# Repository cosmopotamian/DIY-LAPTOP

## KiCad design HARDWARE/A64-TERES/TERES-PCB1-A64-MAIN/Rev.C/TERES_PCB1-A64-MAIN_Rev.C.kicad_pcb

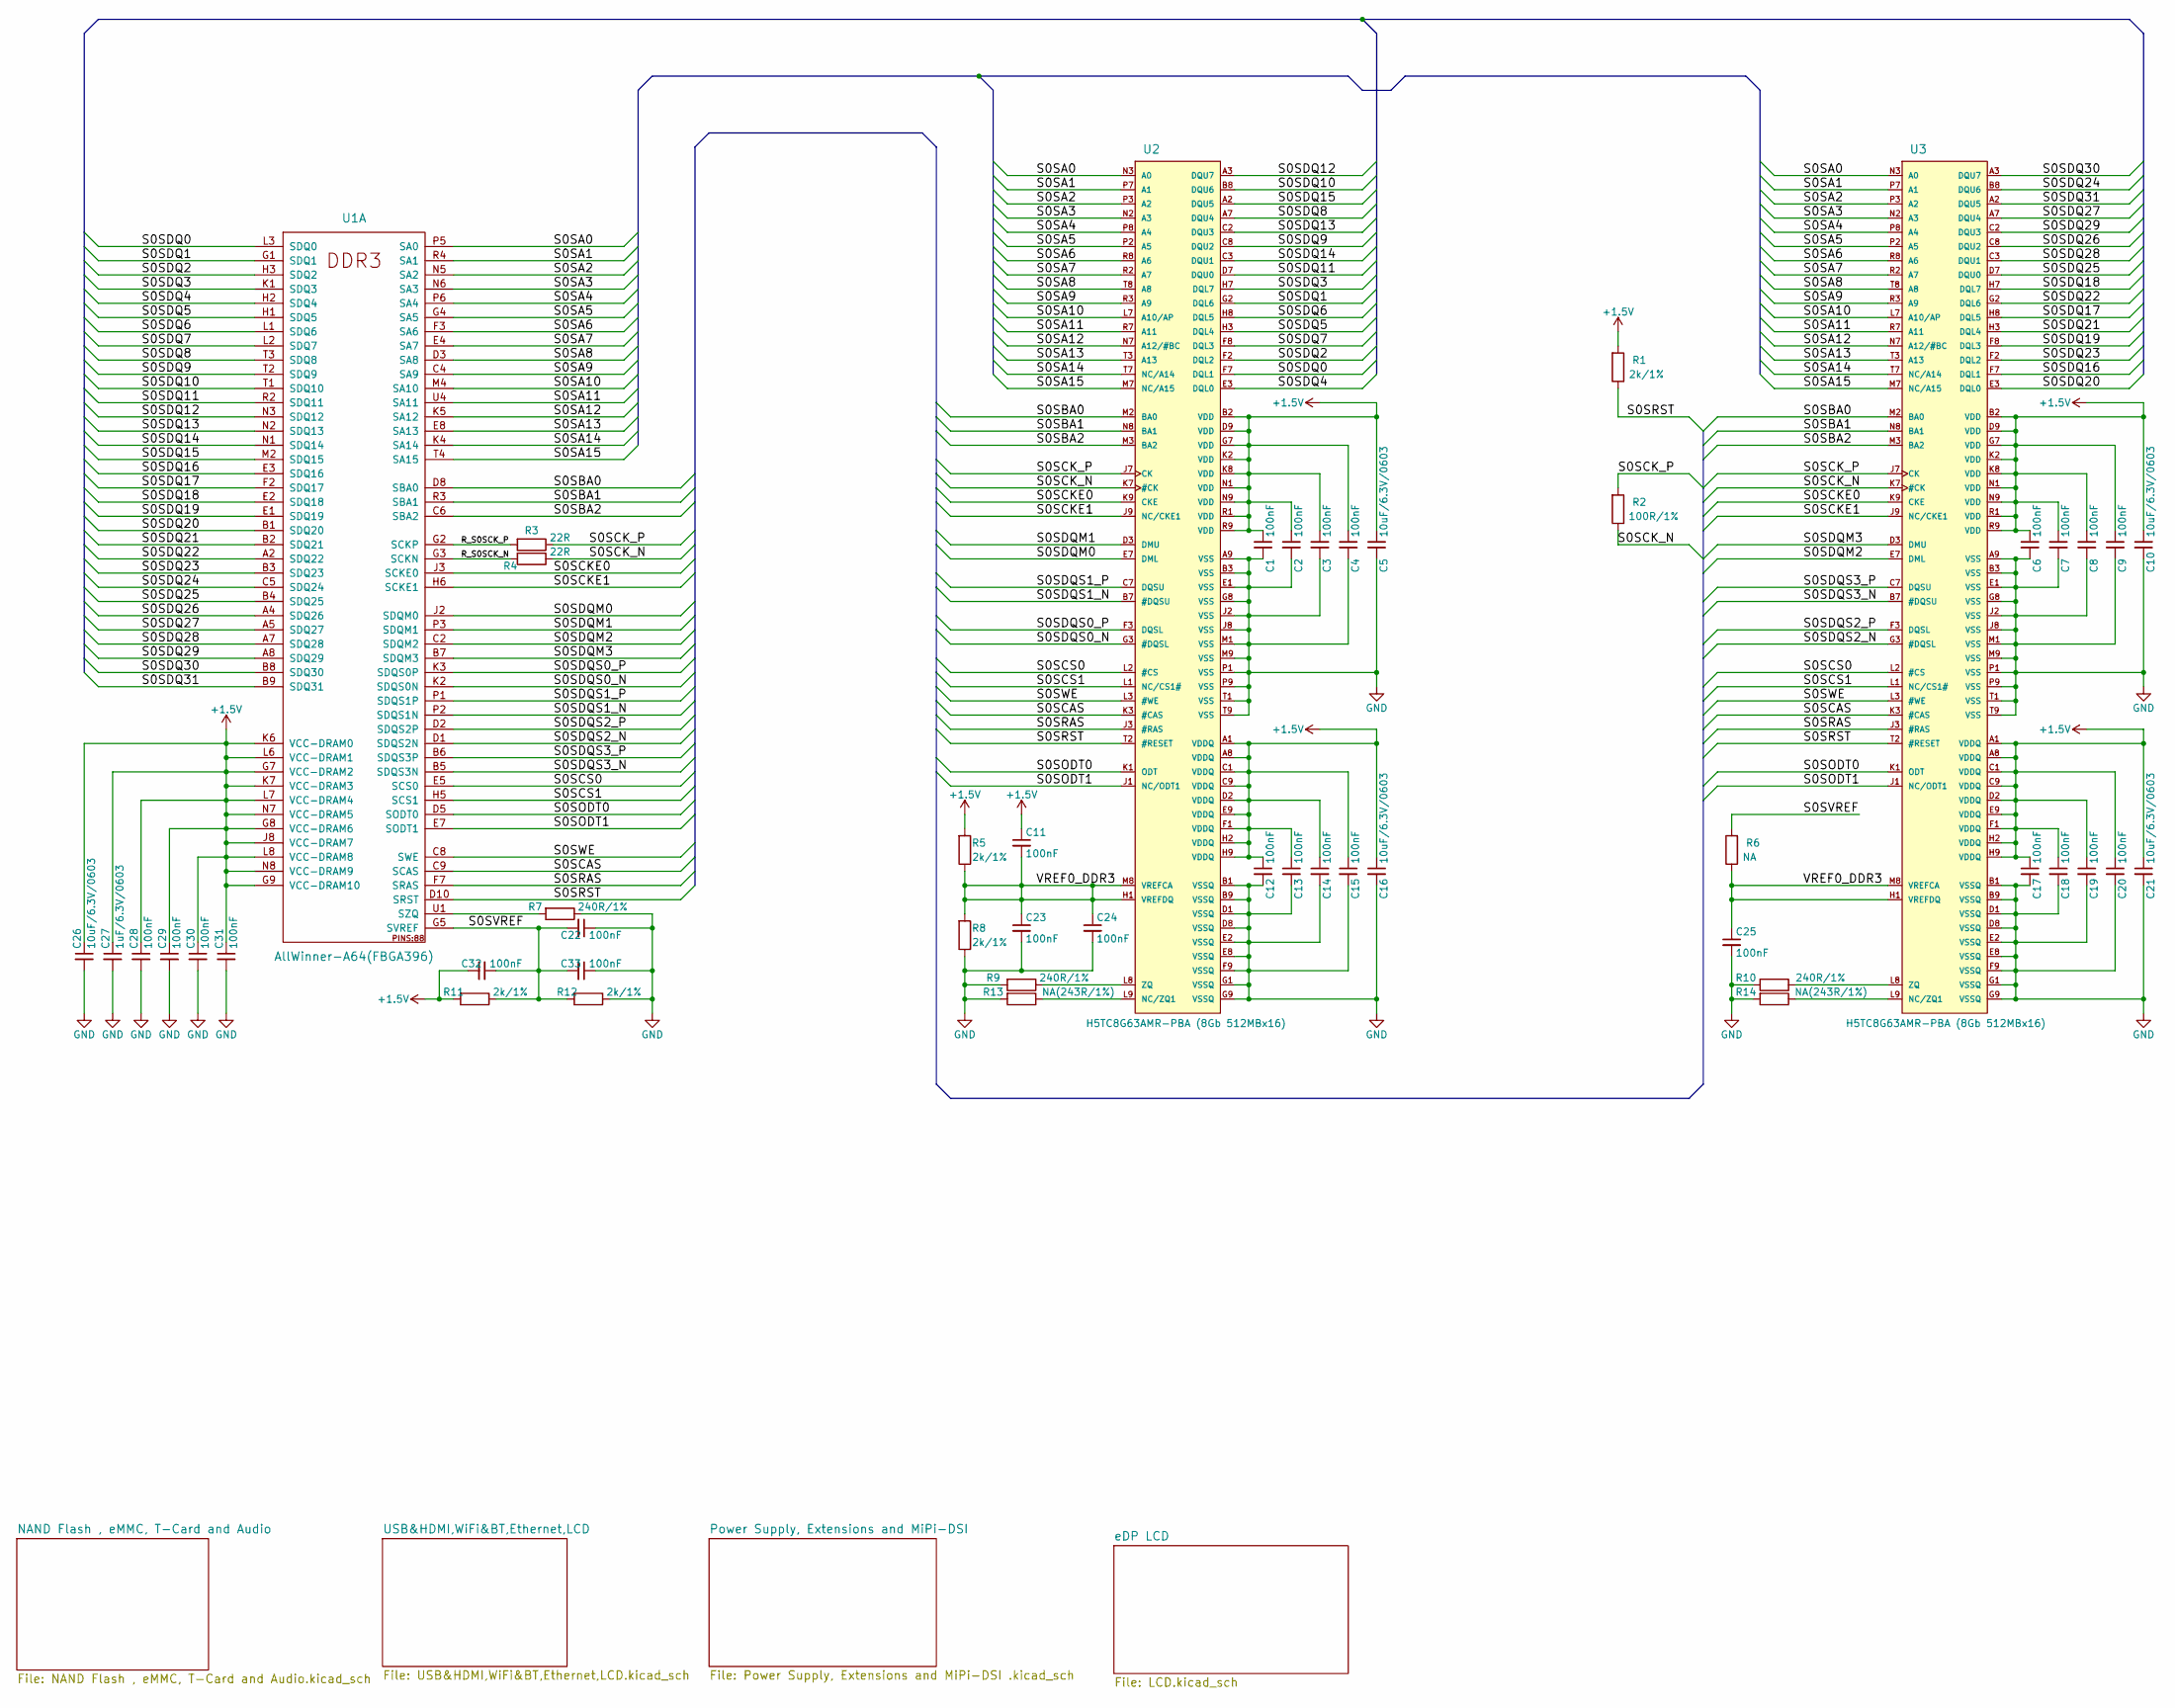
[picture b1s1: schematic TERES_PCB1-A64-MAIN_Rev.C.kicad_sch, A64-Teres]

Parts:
C1, C2, C3, C4, C6, C7, C8, C9, C11, C12, C13, C14, C15, C17, C18, C19, C20, C22, C23, C24, C25, C28, C29, C30, C31, C32, C33: 100nF; C_0402_5MIL_DWS
C5, C10, C16, C21, C26: 10uF/6.3V/0603; C_0603_5MIL_DWS
C27: 1uF/6.3V/0603; C_0603_5MIL_DWS
R1, R5, R8, R11, R12: 2k/1%; R_0402_5MIL_DWS
R2: 100R/1%; R_0402_5MIL_DWS
R3, R4: 22R; R_0402_5MIL_DWS
R6: NA; R_0402_5MIL_DWS
R7, R9, R10: 240R/1%; R_0402_5MIL_DWS
R13, R14: NA(243R/1%); R_0402_5MIL_DWS
U1: AllWinner-A64(FBGA396); FBGA396
U2, U3: H5TC8G63AMR-PBA (8Gb 512MBx16); FBGA96(HYNIX_SAMSUNG_512MX16_DDR3)

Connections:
+1.5V: C1.1, C2.1, C3.1, C4.1, C5.1, C6.1, C7.1, C8.1, C9.1, C10.1, C11.1, C12.1, C13.1, C14.1, C15.1, C16.1, C17.1, C18.1, C19.1, C20.1, C21.1, C26.1, C27.1, C28.1, C29.1, C30.1, C31.1, C32.2, R1.2, R5.2, R11.2, U1.G7 (VCC-DRAM2), U1.G8 (VCC-DRAM6), U1.G9 (VCC-DRAM10), U1.J8 (VCC-DRAM7), U1.K6 (VCC-DRAM0), U1.K7 (VCC-DRAM3), U1.L6 (VCC-DRAM1), U1.L7 (VCC-DRAM4), U1.L8 (VCC-DRAM8), U1.N7 (VCC-DRAM5), U1.N8 (VCC-DRAM9), U2.A1 (VDDQ), U2.A8 (VDDQ), U2.B2 (VDD), U2.C1 (VDDQ), U2.C9 (VDDQ), U2.D2 (VDDQ), U2.D9 (VDD), U2.E9 (VDDQ), U2.F1 (VDDQ), U2.G7 (VDD), U2.H2 (VDDQ), U2.H9 (VDDQ), U2.K2 (VDD), U2.K8 (VDD), U2.N1 (VDD), U2.N9 (VDD), U2.R1 (VDD), U2.R9 (VDD), U3.A1 (VDDQ), U3.A8 (VDDQ), U3.B2 (VDD), U3.C1 (VDDQ), U3.C9 (VDDQ), U3.D2 (VDDQ), U3.D9 (VDD), U3.E9 (VDDQ), U3.F1 (VDDQ), U3.G7 (VDD), U3.H2 (VDDQ), U3.H9 (VDDQ), U3.K2 (VDD), U3.K8 (VDD), U3.N1 (VDD), U3.N9 (VDD), U3.R1 (VDD), U3.R9 (VDD); also elsewhere on the board
/R_S0SCK_N: R4.2, U1.G3 (SCKN)
/R_S0SCK_P: R3.2, U1.G2 (SCKP)
/S0SA0: U1.P5 (SA0), U2.N3 (A0), U3.N3 (A0)
/S0SA1: U1.R4 (SA1), U2.P7 (A1), U3.P7 (A1)
/S0SA2: U1.N5 (SA2), U2.P3 (A2), U3.P3 (A2)
/S0SA3: U1.N6 (SA3), U2.N2 (A3), U3.N2 (A3)
/S0SA4: U1.P6 (SA4), U2.P8 (A4), U3.P8 (A4)
/S0SA5: U1.G4 (SA5), U2.P2 (A5), U3.P2 (A5)
/S0SA6: U1.F3 (SA6), U2.R8 (A6), U3.R8 (A6)
/S0SA7: U1.E4 (SA7), U2.R2 (A7), U3.R2 (A7)
/S0SA8: U1.D3 (SA8), U2.T8 (A8), U3.T8 (A8)
/S0SA9: U1.C4 (SA9), U2.R3 (A9), U3.R3 (A9)
/S0SA10: U1.M4 (SA10), U2.L7 (A10/AP), U3.L7 (A10/AP)
/S0SA11: U1.U4 (SA11), U2.R7 (A11), U3.R7 (A11)
/S0SA12: U1.K5 (SA12), U2.N7 (A12/#BC), U3.N7 (A12/#BC)
/S0SA13: U1.E8 (SA13), U2.T3 (A13), U3.T3 (A13)
/S0SA14: U1.K4 (SA14), U2.T7 (NC/A14), U3.T7 (NC/A14)
/S0SA15: U1.T4 (SA15), U2.M7 (NC/A15), U3.M7 (NC/A15)
/S0SBA0: U1.D8 (SBA0), U2.M2 (BA0), U3.M2 (BA0)
/S0SBA1: U1.R3 (SBA1), U2.N8 (BA1), U3.N8 (BA1)
/S0SBA2: U1.C6 (SBA2), U2.M3 (BA2), U3.M3 (BA2)
/S0SCAS: U1.C9 (SCAS), U2.K3 (#CAS), U3.K3 (#CAS)
/S0SCKE0: U1.J3 (SCKE0), U2.K9 (CKE), U3.K9 (CKE)
/S0SCKE1: U1.H6 (SCKE1), U2.J9 (NC/CKE1), U3.J9 (NC/CKE1)
/S0SCK_N: R2.1, R4.1, U2.K7 (#CK), U3.K7 (#CK)
/S0SCK_P: R2.2, R3.1, U2.J7 (CK), U3.J7 (CK)
/S0SCS0: U1.E5 (SCS0), U2.L2 (#CS), U3.L2 (#CS)
/S0SCS1: U1.H5 (SCS1), U2.L1 (NC/CS1#), U3.L1 (NC/CS1#)
/S0SDQ0: U1.L3 (SDQ0), U2.F7 (DQL1)
/S0SDQ1: U1.G1 (SDQ1), U2.G2 (DQL6)
/S0SDQ2: U1.H3 (SDQ2), U2.F2 (DQL2)
/S0SDQ3: U1.K1 (SDQ3), U2.H7 (DQL7)
/S0SDQ4: U1.H2 (SDQ4), U2.E3 (DQL0)
/S0SDQ5: U1.H1 (SDQ5), U2.H3 (DQL4)
/S0SDQ6: U1.L1 (SDQ6), U2.H8 (DQL5)
/S0SDQ7: U1.L2 (SDQ7), U2.F8 (DQL3)
/S0SDQ8: U1.T3 (SDQ8), U2.A7 (DQU4)
/S0SDQ9: U1.T2 (SDQ9), U2.C8 (DQU2)
/S0SDQ10: U1.T1 (SDQ10), U2.B8 (DQU6)
/S0SDQ11: U1.R2 (SDQ11), U2.D7 (DQU0)
/S0SDQ12: U1.N3 (SDQ12), U2.A3 (DQU7)
/S0SDQ13: U1.N2 (SDQ13), U2.C2 (DQU3)
/S0SDQ14: U1.N1 (SDQ14), U2.C3 (DQU1)
/S0SDQ15: U1.M2 (SDQ15), U2.A2 (DQU5)
/S0SDQ16: U1.E3 (SDQ16), U3.F7 (DQL1)
/S0SDQ17: U1.F2 (SDQ17), U3.H8 (DQL5)
/S0SDQ18: U1.E2 (SDQ18), U3.H7 (DQL7)
/S0SDQ19: U1.E1 (SDQ19), U3.F8 (DQL3)
/S0SDQ20: U1.B1 (SDQ20), U3.E3 (DQL0)
/S0SDQ21: U1.B2 (SDQ21), U3.H3 (DQL4)
/S0SDQ22: U1.A2 (SDQ22), U3.G2 (DQL6)
/S0SDQ23: U1.B3 (SDQ23), U3.F2 (DQL2)
/S0SDQ24: U1.C5 (SDQ24), U3.B8 (DQU6)
/S0SDQ25: U1.B4 (SDQ25), U3.D7 (DQU0)
/S0SDQ26: U1.A4 (SDQ26), U3.C8 (DQU2)
/S0SDQ27: U1.A5 (SDQ27), U3.A7 (DQU4)
/S0SDQ28: U1.A7 (SDQ28), U3.C3 (DQU1)
/S0SDQ29: U1.A8 (SDQ29), U3.C2 (DQU3)
/S0SDQ30: U1.B8 (SDQ30), U3.A3 (DQU7)
/S0SDQ31: U1.B9 (SDQ31), U3.A2 (DQU5)
/S0SDQM0: U1.J2 (SDQM0), U2.E7 (DML)
/S0SDQM1: U1.P3 (SDQM1), U2.D3 (DMU)
/S0SDQM2: U1.C2 (SDQM2), U3.E7 (DML)
/S0SDQM3: U1.B7 (SDQM3), U3.D3 (DMU)
/S0SDQS0_N: U1.K2 (SDQS0N), U2.G3 (#DQSL)
/S0SDQS0_P: U1.K3 (SDQS0P), U2.F3 (DQSL)
/S0SDQS1_N: U1.P2 (SDQS1N), U2.B7 (#DQSU)
/S0SDQS1_P: U1.P1 (SDQS1P), U2.C7 (DQSU)
/S0SDQS2_N: U1.D1 (SDQS2N), U3.G3 (#DQSL)
/S0SDQS2_P: U1.D2 (SDQS2P), U3.F3 (DQSL)
/S0SDQS3_N: U1.B5 (SDQS3N), U3.B7 (#DQSU)
/S0SDQS3_P: U1.B6 (SDQS3P), U3.C7 (DQSU)
/S0SODT0: U1.D5 (SODT0), U2.K1 (ODT), U3.K1 (ODT)
/S0SODT1: U1.E7 (SODT1), U2.J1 (NC/ODT1), U3.J1 (NC/ODT1)
/S0SRAS: U1.F7 (SRAS), U2.J3 (#RAS), U3.J3 (#RAS)
/S0SRST: R1.1, U1.D10 (SRST), U2.T2 (#RESET), U3.T2 (#RESET)
/S0SVREF: C22.2, C32.1, C33.2, R6.2, R11.1, R12.2, U1.G5 (SVREF)
/S0SWE: U1.C8 (SWE), U2.L3 (#WE), U3.L3 (#WE)
/VREF0_DDR3: C11.2, C23.1, C24.1, C25.1, R5.1, R6.1, R8.2, U2.H1 (VREFDQ), U2.M8 (VREFCA), U3.H1 (VREFDQ), U3.M8 (VREFCA)
GND: C1.2, C2.2, C3.2, C4.2, C5.2, C6.2, C7.2, C8.2, C9.2, C10.2, C12.2, C13.2, C14.2, C15.2, C16.2, C17.2, C18.2, C19.2, C20.2, C21.2, C22.1, C23.2, C24.2, C25.2, C26.2, C27.2, C28.2, C29.2, C30.2, C31.2, C33.1, R7.1, R8.1, R9.2, R10.2, R12.1, R13.2, R14.2, U2.A9 (VSS), U2.B1 (VSSQ), U2.B3 (VSS), U2.B9 (VSSQ), U2.D1 (VSSQ), U2.D8 (VSSQ), U2.E1 (VSS), U2.E2 (VSSQ), U2.E8 (VSSQ), U2.F9 (VSSQ), U2.G1 (VSSQ), U2.G8 (VSS), U2.G9 (VSSQ), U2.J2 (VSS), U2.J8 (VSS), U2.M1 (VSS), U2.M9 (VSS), U2.P1 (VSS), U2.P9 (VSS), U2.T1 (VSS), U2.T9 (VSS), U3.A9 (VSS), U3.B1 (VSSQ), U3.B3 (VSS), U3.B9 (VSSQ), U3.D1 (VSSQ), U3.D8 (VSSQ), U3.E1 (VSS), U3.E2 (VSSQ), U3.E8 (VSSQ), U3.F9 (VSSQ), U3.G1 (VSSQ), U3.G8 (VSS), U3.G9 (VSSQ), U3.J2 (VSS), U3.J8 (VSS), U3.M1 (VSS), U3.M9 (VSS), U3.P1 (VSS), U3.P9 (VSS), U3.T1 (VSS), U3.T9 (VSS); also elsewhere on the board
unnamed: R7.2, U1.U1 (SZQ)
unnamed: R9.1, U2.L8 (ZQ)
unnamed: R10.1, U3.L8 (ZQ)
unnamed: R13.1, U2.L9 (NC/ZQ1)
unnamed: R14.1, U3.L9 (NC/ZQ1)

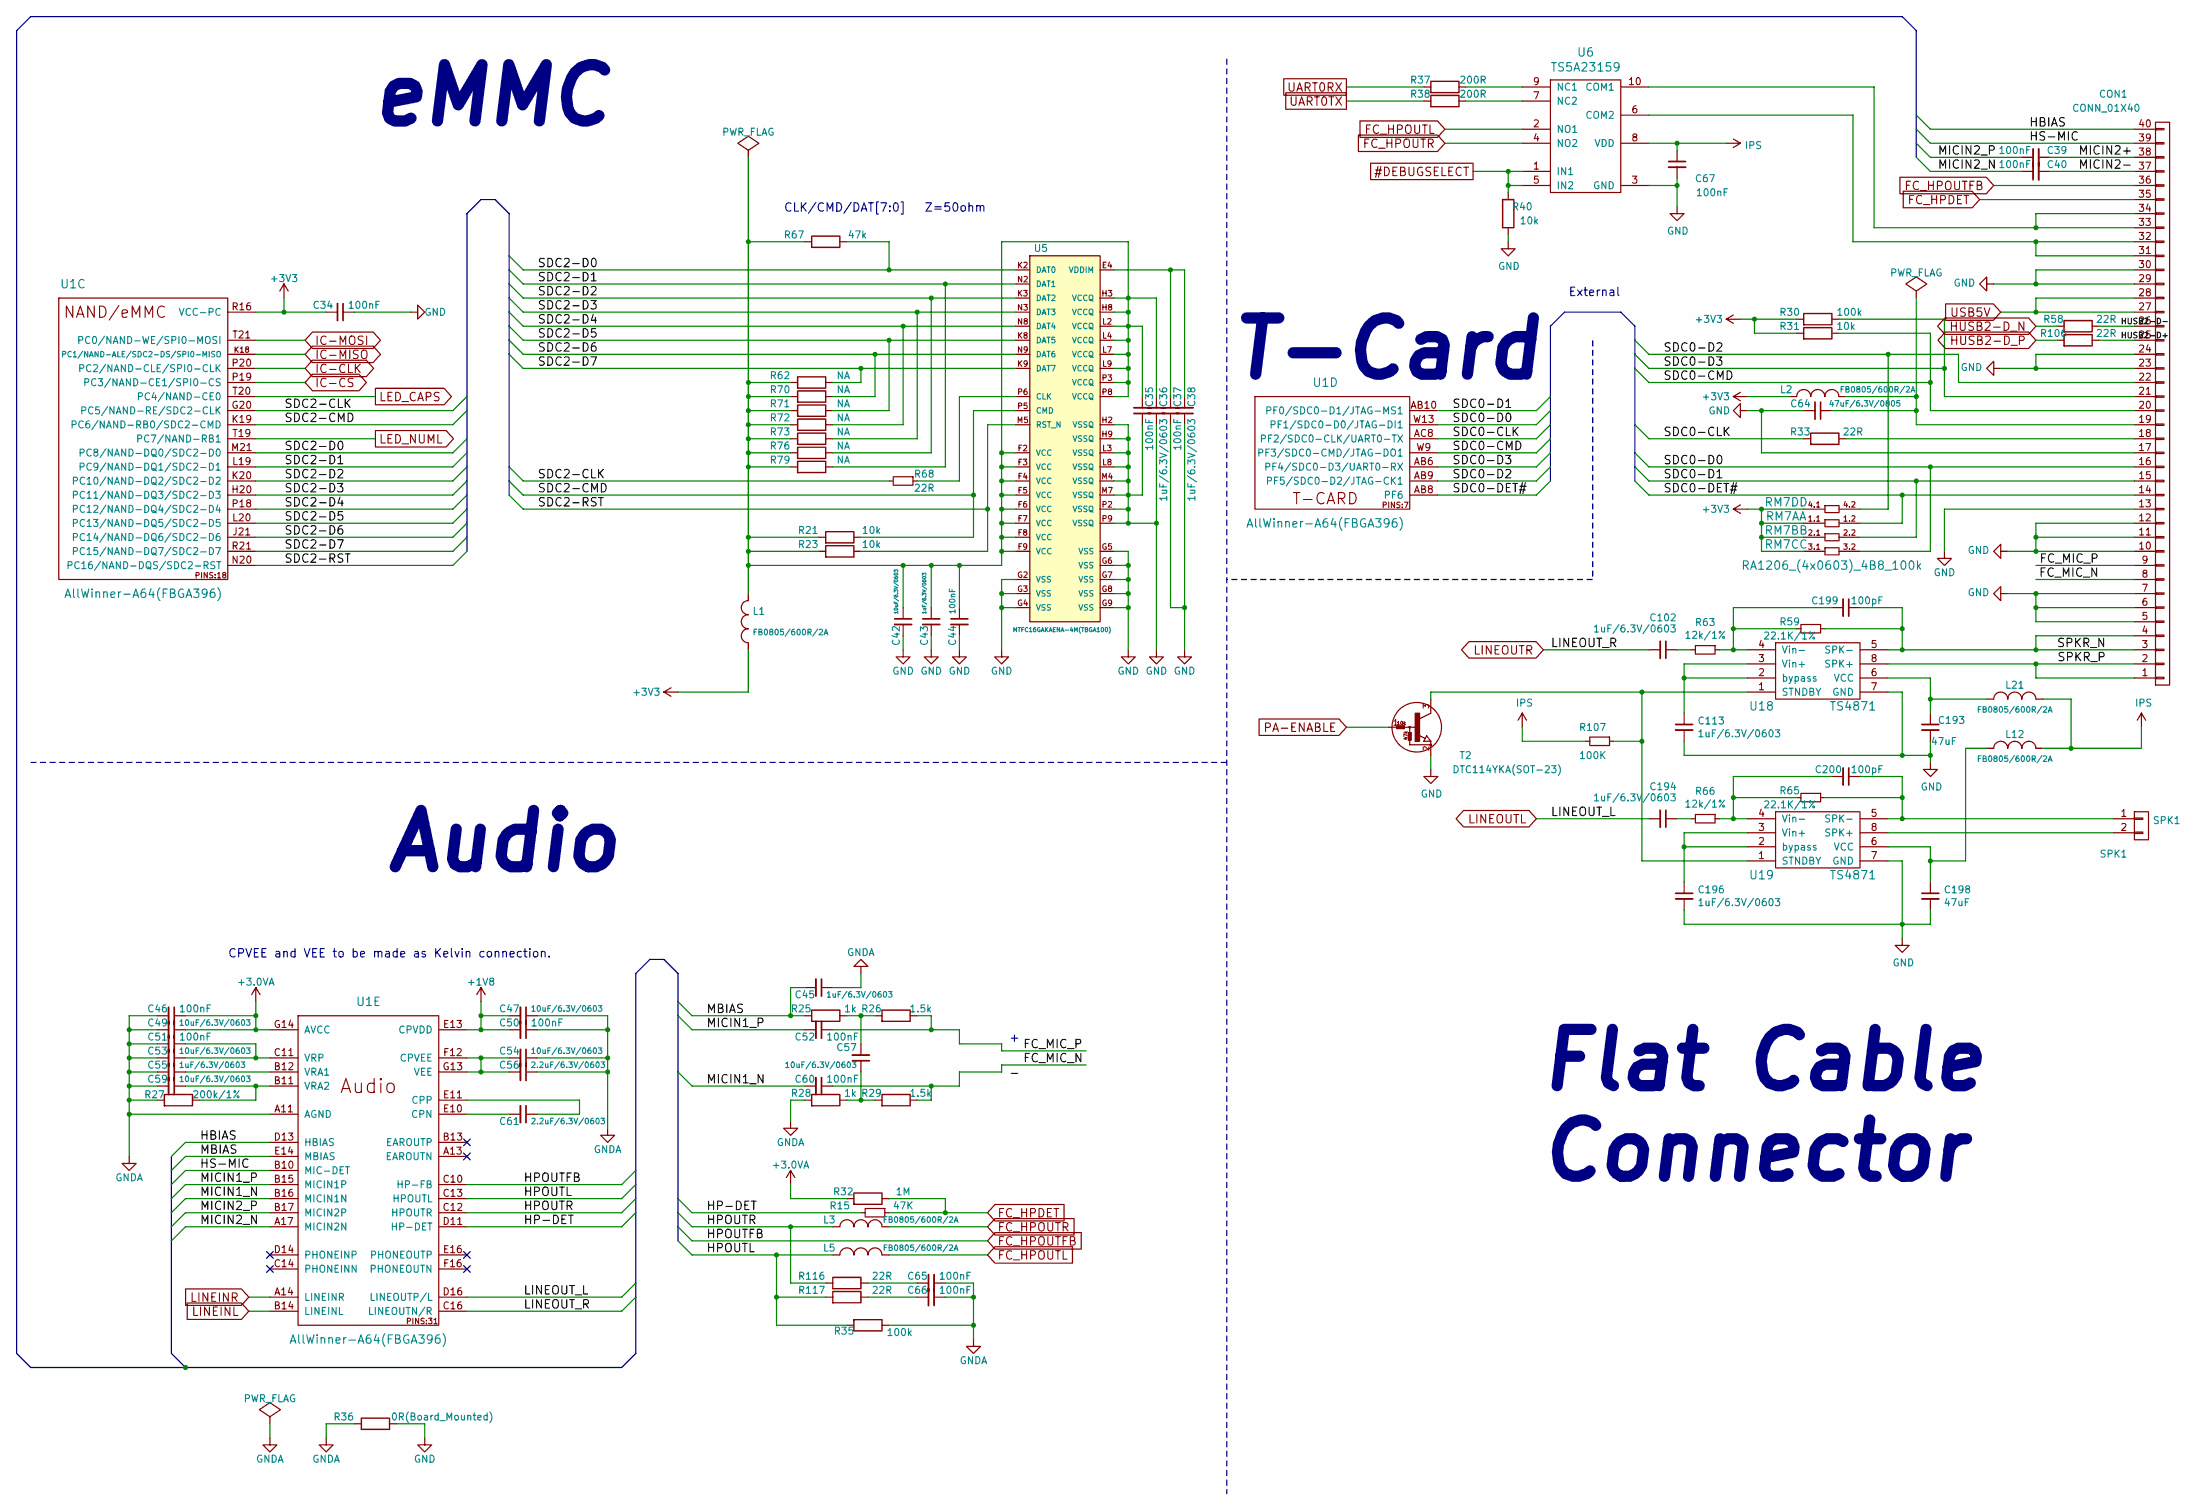
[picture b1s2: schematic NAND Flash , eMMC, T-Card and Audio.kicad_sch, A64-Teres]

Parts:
C34, C35, C37, C39, C40, C44, C46, C50, C51, C52, C60, C65, C66, C67: 100nF; C_0402_5MIL_DWS
C36, C38, C43, C45, C55, C102, C113, C194, C196: 1uF/6.3V/0603; C_0603_5MIL_DWS
C42, C47, C49, C53, C54, C57, C59: 10uF/6.3V/0603; C_0603_5MIL_DWS
C56, C61: 2.2uF/6.3V/0603; C_0603_5MIL_DWS
C64: 47uF/6.3V/0805; C_0805_5MIL_DWS
C193, C198: 47uF; C_0805_5MIL_DWS
C199, C200: 100pF; C_0402_5MIL_DWS
CON1: CONN_01X40; FPV-WZA21-40-LF
L1, L2, L3, L5, L12, L21: FB0805/600R/2A; L_0805_5MIL_DWS
R15: 47K; R_0402_5MIL_DWS
R21, R23, R31, R40: 10k; R_0402_5MIL_DWS
R25, R28: 1k; R_0402_5MIL_DWS
R26, R29: 1.5k; R_0402_5MIL_DWS
R27: 200k/1%; R_0402_5MIL_DWS
R30, R35: 100k; R_0402_5MIL_DWS
R32: 1M; R_0402_5MIL_DWS
R33, R58, R68, R106, R116, R117: 22R; R_0402_5MIL_DWS
R36: 0R(Board_Mounted); 0R_0603
R37, R38: 200R; R_0402_5MIL_DWS
R59, R65: 22.1K/1%; R_0402_5MIL_DWS
R62, R70, R71, R72, R73, R76, R79: NA; R_0402_5MIL_DWS
R63, R66: 12k/1%; R_0402_5MIL_DWS
R67: 47k; R_0402_5MIL_DWS
R107: 100K; R_0402_5MIL_DWS
RM7A, RM7B: RA1206_(4x0603)_4B8_100k; R_MATRIX_4
RM7C, RM7D: RA1206_(4x0603)_4B8_100k; RA1206_(4X0603)_4B8_xx
SPK1: SPK1; CON-SPK-TERES
T2: DTC114YKA(SOT-23); SOT23
U1: AllWinner-A64(FBGA396); FBGA396
U5: MTFC16GAKAENA-4M(TBGA100); TBGA100
U6: TS5A23159; VSSOP-10
U18, U19: TS4871; SO-8

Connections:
#DEBUGSELECT: R40.2, U6.1 (IN1), U6.5 (IN2); also elsewhere on the board
+1V8: C47.2, C50.2, U1.E13 (CPVDD); also elsewhere on the board
+3.0VA: C46.1, C49.1, R32.2, U1.G14 (AVCC); also elsewhere on the board
+3V3: C34.2, L1.1, L2.1, R30.2, R31.2, RM7A.1.1, RM7B.2.1, RM7C.3.1, RM7D.4.1, U1.R16 (VCC-PC); also elsewhere on the board
/NAND Flash , eMMC, T-Card and Audio/FC_MIC_N: C60.1, CON1.8, R29.1
/NAND Flash , eMMC, T-Card and Audio/FC_MIC_P: C52.1, CON1.9, R26.1
/NAND Flash , eMMC, T-Card and Audio/HBIAS: CON1.40, U1.D13 (HBIAS)
/NAND Flash , eMMC, T-Card and Audio/HP-DET: R15.2, U1.D11 (HP-DET)
/NAND Flash , eMMC, T-Card and Audio/HPOUTL: L5.1, R35.2, R117.2, U1.C13 (HPOUTL)
/NAND Flash , eMMC, T-Card and Audio/HPOUTR: L3.1, R116.2, U1.C12 (HPOUTR)
/NAND Flash , eMMC, T-Card and Audio/HS-MIC: CON1.39, U1.B10 (MIC-DET)
/NAND Flash , eMMC, T-Card and Audio/HUSB2-D+: CON1.25, R106.1
/NAND Flash , eMMC, T-Card and Audio/HUSB2-D-: CON1.26, R58.1
/NAND Flash , eMMC, T-Card and Audio/MBIAS: C45.2, R25.2, U1.E14 (MBIAS)
/NAND Flash , eMMC, T-Card and Audio/MICIN1_N: C60.2, U1.B16 (MICIN1N)
/NAND Flash , eMMC, T-Card and Audio/MICIN1_P: C52.2, U1.B15 (MICIN1P)
/NAND Flash , eMMC, T-Card and Audio/MICIN2+: C39.2, CON1.38
/NAND Flash , eMMC, T-Card and Audio/MICIN2-: C40.2, CON1.37
/NAND Flash , eMMC, T-Card and Audio/MICIN2_N: C40.1, U1.A17 (MICIN2N)
/NAND Flash , eMMC, T-Card and Audio/MICIN2_P: C39.1, U1.B17 (MICIN2P)
/NAND Flash , eMMC, T-Card and Audio/SDC0-CLK: R33.2, U1.AC8 (PF2/SDC0-CLK/UART0-TX)
/NAND Flash , eMMC, T-Card and Audio/SDC0-CMD: CON1.20, R31.1, U1.W9 (PF3/SDC0-CMD/JTAG-DO1)
/NAND Flash , eMMC, T-Card and Audio/SDC0-D0: CON1.16, RM7C.3.2, U1.W13 (PF1/SDC0-D0/JTAG-DI1); also elsewhere on the board
/NAND Flash , eMMC, T-Card and Audio/SDC0-D1: CON1.15, RM7B.2.2, U1.AB10 (PF0/SDC0-D1/JTAG-MS1); also elsewhere on the board
/NAND Flash , eMMC, T-Card and Audio/SDC0-D2: CON1.22, RM7D.4.2, U1.AB9 (PF5/SDC0-D2/JTAG-CK1); also elsewhere on the board
/NAND Flash , eMMC, T-Card and Audio/SDC0-D3: CON1.21, R30.1, U1.AB6 (PF4/SDC0-D3/UART0-RX)
/NAND Flash , eMMC, T-Card and Audio/SDC0-DET#: CON1.14, RM7A.1.2, U1.AB8 (PF6); also elsewhere on the board
/NAND Flash , eMMC, T-Card and Audio/SDC2-CLK: R68.2, U1.G20 (PC5/NAND-RE/SDC2-CLK)
/NAND Flash , eMMC, T-Card and Audio/SDC2-CMD: R21.1, U1.K19 (PC6/NAND-RB0/SDC2-CMD), U5.P5 (CMD)
/NAND Flash , eMMC, T-Card and Audio/SDC2-D0: R67.1, U1.M21 (PC8/NAND-DQ0/SDC2-D0), U5.K2 (DAT0)
/NAND Flash , eMMC, T-Card and Audio/SDC2-D1: R79.1, U1.L19 (PC9/NAND-DQ1/SDC2-D1), U5.N2 (DAT1)
/NAND Flash , eMMC, T-Card and Audio/SDC2-D2: R76.1, U1.K20 (PC10/NAND-DQ2/SDC2-D2), U5.K3 (DAT2)
/NAND Flash , eMMC, T-Card and Audio/SDC2-D3: R73.1, U1.H20 (PC11/NAND-DQ3/SDC2-D3), U5.N3 (DAT3)
/NAND Flash , eMMC, T-Card and Audio/SDC2-D4: R72.1, U1.P18 (PC12/NAND-DQ4/SDC2-D4), U5.N8 (DAT4)
/NAND Flash , eMMC, T-Card and Audio/SDC2-D5: R71.1, U1.L20 (PC13/NAND-DQ5/SDC2-D5), U5.K8 (DAT5)
/NAND Flash , eMMC, T-Card and Audio/SDC2-D6: R70.1, U1.J21 (PC14/NAND-DQ6/SDC2-D6), U5.N9 (DAT6)
/NAND Flash , eMMC, T-Card and Audio/SDC2-D7: R62.1, U1.R21 (PC15/NAND-DQ7/SDC2-D7), U5.K9 (DAT7)
/NAND Flash , eMMC, T-Card and Audio/SDC2-RST: R23.1, U1.N20 (PC16/NAND-DQS/SDC2-RST), U5.M5 (RST_N)
/NAND Flash , eMMC, T-Card and Audio/SPKR_N: C199.1, CON1.3, CON1.4, R59.1, U18.5 (SPK-)
/NAND Flash , eMMC, T-Card and Audio/SPKR_P: CON1.1, CON1.2, U18.8 (SPK+)
FC_HPDET: CON1.35, R15.1, R32.1
FC_HPOUTFB: CON1.36, U1.C10 (HP-FB)
FC_HPOUTL: L5.2, U6.2 (NO1)
FC_HPOUTR: L3.2, U6.4 (NO2)
GND: C34.1, C35.1, C36.1, C37.1, C38.1, C42.2, C43.2, C44.2, C64.2, C67.2, C113.2, C193.2, C196.2, C198.2, CON1.0, CON1.5, CON1.6, CON1.7, CON1.10, CON1.11, CON1.12, CON1.13, CON1.17, CON1.23, CON1.24, CON1.29, CON1.30, R36.1, R40.1, SPK1.0, T2.2 (E), U5.G2 (VSS), U5.G3 (VSS), U5.G4 (VSS), U5.G5 (VSS), U5.G6 (VSS), U5.G7 (VSS), U5.G8 (VSS), U5.G9 (VSS), U5.H2 (VSSQ), U5.H9 (VSSQ), U5.L3 (VSSQ), U5.L8 (VSSQ), U5.M4 (VSSQ), U5.M7 (VSSQ), U5.P2 (VSSQ), U5.P9 (VSSQ), U6.3 (GND), U18.7 (GND), U19.7 (GND); also elsewhere on the board
GNDA: C45.1, C46.2, C47.1, C49.2, C50.1, C51.2, C53.2, C54.1, C55.2, C56.1, C59.2, C65.1, C66.1, R27.2, R28.2, R35.1, R36.2, U1.A11 (AGND)
HUSB2-D_N: R58.2; also elsewhere on the board
HUSB2-D_P: R106.2; also elsewhere on the board
IC-CLK: U1.P20 (PC2/NAND-CLE/SPI0-CLK); also elsewhere on the board
IC-CS: U1.P19 (PC3/NAND-CE1/SPI0-CS); also elsewhere on the board
IC-MISO: U1.K18 (PC1/NAND-ALE/SDC2-DS/SPI0-MISO); also elsewhere on the board
IC-MOSI: U1.T21 (PC0/NAND-WE/SPI0-MOSI); also elsewhere on the board
IPS: C67.1, L12.2, L21.2, R107.2, U6.8 (VDD); also elsewhere on the board
LED_CAPS: U1.T20 (PC4/NAND-CE0); also elsewhere on the board
LED_NUML: U1.T19 (PC7/NAND-RB1); also elsewhere on the board
LINEINL: U1.B14 (LINEINL); also elsewhere on the board
LINEINR: U1.A14 (LINEINR); also elsewhere on the board
LINEOUTL: C194.2, U1.D16 (LINEOUTP/L); also elsewhere on the board
LINEOUTR: C102.2, U1.C16 (LINEOUTN/R); also elsewhere on the board
unnamed: C35.2, C36.2, C42.1, C43.1, C44.1, L1.2, R21.2, R23.2, R62.2, R67.2, R70.2, R71.2, R72.2, R73.2, R76.2, R79.2, U5.F2 (VCC), U5.F3 (VCC), U5.F4 (VCC), U5.F5 (VCC), U5.F6 (VCC), U5.F7 (VCC), U5.F8 (VCC), U5.F9 (VCC), U5.H3 (VCCQ), U5.H8 (VCCQ), U5.L2 (VCCQ), U5.L4 (VCCQ), U5.L7 (VCCQ), U5.L9 (VCCQ), U5.P3 (VCCQ), U5.P8 (VCCQ)
unnamed: C37.2, C38.2, U5.E4 (VDDIM)
unnamed: C51.1, C53.1, U1.C11 (VRP)
unnamed: C54.2, C56.2, U1.F12 (CPVEE), U1.G13 (VEE)
unnamed: C55.1, U1.B12 (VRA1)
unnamed: C57.1, R28.1, R29.2
unnamed: C57.2, R25.1, R26.2
unnamed: C59.1, R27.1, U1.B11 (VRA2)
unnamed: C61.1, U1.E11 (CPP)
unnamed: C61.2, U1.E10 (CPN)
unnamed: C64.1, CON1.19, L2.2
unnamed: C65.2, R116.1
unnamed: C66.2, R117.1
unnamed: C102.1, R63.2
unnamed: C113.1, U18.2 (bypass), U18.3 (Vin+)
unnamed: C193.1, L21.1, U18.6 (VCC)
unnamed: C194.1, R66.2
unnamed: C196.1, U19.2 (bypass), U19.3 (Vin+)
unnamed: C198.1, L12.1, U19.6 (VCC)
unnamed: C199.2, R59.2, R63.1, U18.4 (Vin-)
unnamed: C200.1, R65.1, SPK1.1, U19.5 (SPK-)
unnamed: C200.2, R65.2, R66.1, U19.4 (Vin-)
unnamed: CON1.18, R33.1
unnamed: CON1.31, CON1.32, U6.6 (COM2)
unnamed: CON1.33, CON1.34, U6.10 (COM1)
unnamed: R37.1, U6.9 (NC1)
unnamed: R38.1, U6.7 (NC2)
unnamed: R68.1, U5.P6 (CLK)
unnamed: R107.1, T2.3 (C), U18.1 (STNDBY), U19.1 (STNDBY)
unnamed: SPK1.2, U19.8 (SPK+)
PA-ENABLE: T2.1 (B); also elsewhere on the board
UART0RX: R37.2; also elsewhere on the board
UART0TX: R38.2; also elsewhere on the board
USB5V: CON1.27, CON1.28; also elsewhere on the board

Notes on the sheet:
Audio
T-Card
CPVEE and VEE to be made as Kelvin connection.
CLK/CMD/DAT[7:0] Z=50ohm
External
eMMC
Flat Cable Connector

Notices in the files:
HARDWARE/A64-TERES/TERES-PCB1-A64-MAIN/Rev.C/TERES_PCB1-A64-MAIN_Rev.C.kicad_pcb:
(C) 2017
